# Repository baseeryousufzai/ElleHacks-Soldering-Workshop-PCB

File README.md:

This repository contains a PCB that is part of a custom kit made for a beginner-friendly soldering workshop for WISE @ York University.

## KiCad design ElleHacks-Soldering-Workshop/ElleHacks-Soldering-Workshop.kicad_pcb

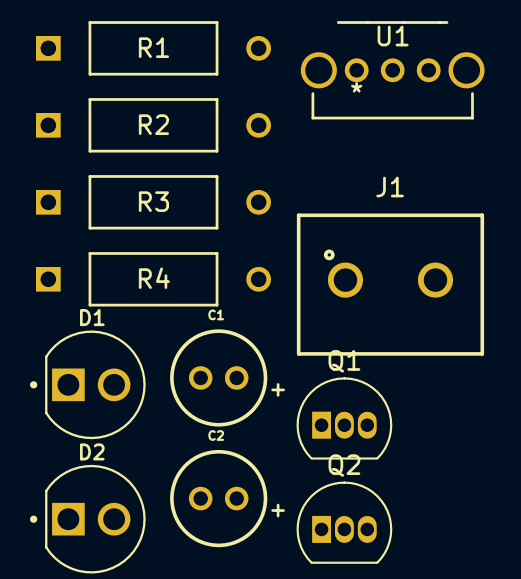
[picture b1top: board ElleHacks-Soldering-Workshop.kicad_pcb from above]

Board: 2 copper layers, 12 parts (0 on the bottom side), 7 nets, no tracks yet.

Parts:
C1, C2: 10 uF; WCAP-ATG8_5X11_DXL_
D1, D2: LED; LEDRD254W57D500H1070
J1: Power Input; 691137710002
Q1, Q2: 2N3904; TO-92_Inline
R1, R4: 470 Ω; YAG_MF25_YAG
R2, R3: 47 kΩ; YAG_MF25_YAG
U1: OS102011MA1QS1; SWITCH_11MA1QS1

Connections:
+9V: J1.2, U1.1
/B1: C1.2, Q2.2 (B), R2.2
/B2: C2.2, Q1.2 (B), R3.2
GND: J1.1, Q1.1 (E), Q2.1 (E)
unnamed: R2.1, R3.1, U1.3
unnamed: C1.1, Q1.3 (C), R1.2
unnamed: C2.1, Q2.3 (C), R4.2

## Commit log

2025-01-27 ElleHacks
2025-01-29 Dark Star
2025-01-29 uploaded assets for logo
